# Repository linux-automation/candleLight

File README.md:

# candleLight

A candleLight is a flash drive sized USB CAN dongle.
It works with the
[candle-usb candleLight firmware](https://github.com/candle-usb/candleLight_fw).

This is a fork of [HubertD's candleLight](https://github.com/HubertD/candleLight)
KiCAD project. Thanks for sharing this awesome design as open hardware!

## Releases

### candlelight-S01-R01

This is our first release for production.

* Added Manufacturer and MPN for key components.
* Added our logo.
* Created manufacturing data.

### V1.1

This is HubertD's original release.

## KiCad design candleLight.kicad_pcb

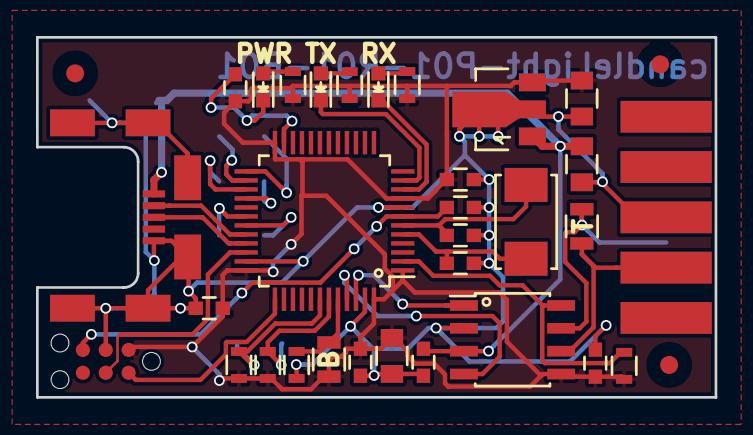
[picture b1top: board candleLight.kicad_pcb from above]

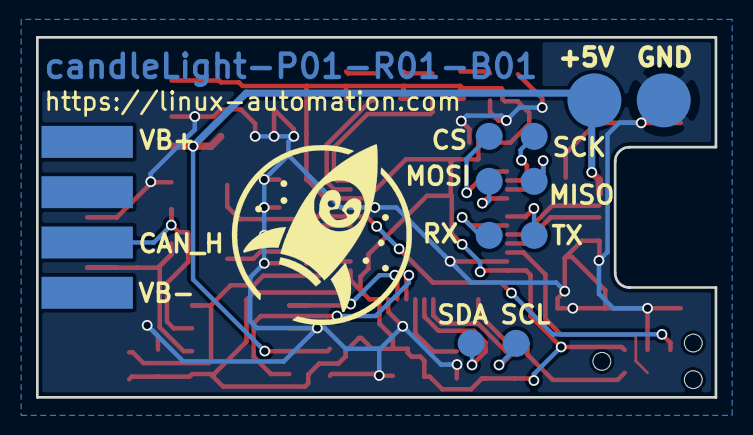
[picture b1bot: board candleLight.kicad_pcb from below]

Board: 2 copper layers, 37.7 x 20.0 mm, 45 parts (11 on the bottom side), 29 nets.

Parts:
C201, C202: 20pF; C_0603
C203, C204, C205, C206, C208, C402, C403: 100nF; C_0603
C207, C301, C303: 10uF; C_0805
D601, D602, D603: LED; LED_0603
FID101, FID102, FID103: Dummy_FIDUCIAL_Passermarke_Type1_RevE_Date16Nov20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; Fiducial_1mm_Dia_2.54mm_Outer_CopperTop
NB101: LAG_logo; lag_rocket_10mmx10.4mm
P501: USB_OTG; Molex-Micro-USB-B-Middle-Mount
R201, R202: 4K7; R_0603
R203: R; R_0805
R204, R601, R602, R603: 1K; R_0603
R401: 10K; R_0603
R402: dnp; R_0805
U201: STM32F072C8Tx; LQFP-48_7x7mm_Pitch0.5mm
U301: MCP1754ST-3302E/MB; SOT89-3_Housing
U401: TJA1051/3; SOIC-8_3.9x4.9mm_Pitch1.27mm
W201, W202, W203, W204, W205, W206, W207, W208: TEST_1P; Measurement_Point_Round-SMD-Pad_Small
W301, W302: TEST_1P; Measurement_Point_Round-SMD-Pad_Big
X501: CON_SWD; TC2030-NL
X502: SUB-D9; DB9M_CI
Y201: 8MHz; ABM3

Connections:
+3V3: C203.1, C204.1, C205.1, C206.1, C207.1, C303.1, C403.1, R201.1, R202.2, R203.1, R401.1, R601.2, R602.2, R603.2, U201.1, U201.9, U201.24, U201.36, U201.48, U301.3, U401.5, X501.1
+5V: C301.1, C402.1, P501.1, U301.1, U401.3, W301.1
/CAN/CAN_H: R402.1, U401.7, X502.7
/CAN/CAN_L: R402.2, U401.6, X502.2
/CAN/CAN_S: R401.2, U201.2, U401.8
/Connectors/NRST: C208.1, U201.7, X501.5
/Connectors/SWCLK: U201.37, X501.2
/Connectors/SWDIO: U201.34, X501.4
/Connectors/USB_DM: P501.2, U201.32
/Connectors/USB_DP: P501.3, U201.33
/LEDs/LED1: D601.1, U201.10
/LEDs/LED2: D602.1, U201.11
/MCU/BOOT0: R203.2, R204.2, U201.44
/MCU/CAN_RX: U201.45, U401.4
/MCU/CAN_TX: U201.46, U401.1
/MCU/CS: U201.25, W205.1
/MCU/MISO: U201.27, W207.1
/MCU/MOSI: U201.28, W208.1
/MCU/RX: U201.31, W202.1
/MCU/SCK: U201.26, W206.1
/MCU/SCL: R201.2, U201.42, W203.1
/MCU/SDA: R202.1, U201.43, W204.1
/MCU/TX: U201.30, W201.1
GND: C201.1, C202.1, C203.2, C204.2, C205.2, C206.2, C207.2, C208.2, C301.2, C303.2, C402.2, C403.2, D603.1, P501.5, P501.6, R204.1, U201.8, U201.23, U201.35, U201.47, U301.2, U401.2, W302.1, X501.3, X502.3
unnamed: C201.2, U201.5, Y201.1
unnamed: C202.2, U201.6, Y201.2
unnamed: D601.2, R601.1
unnamed: D602.2, R602.1
unnamed: D603.2, R603.1

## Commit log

2021-03-03 Perform automatic KiCAD rescue operations
2021-03-03 Add Linux Automation page layout
2021-03-03 Add Fit, Manufacturer, MPN fields
2021-03-04 Update Silkscreen and add netnames
2021-03-04 Add Cap voltage rating, Put PCB ref on cupper, add note for variants
2021-03-04 Add linux automation logo
2021-03-05 Create release candlelight-S01-R01
2021-03-08 Fix candlelight-S01-R01-V03: mixup USB/D-SUB
2021-03-08 Remove original manufacturing data
    The original manufacturing data does not match our
    versioning scheme and we are not going to support
    hardware manufactured based on it.
    Remove it to prevent confusing people looking for
    the manufacturing data corresponding to the product
    they bought in our shop.
2021-03-08 Add PnP information to SMT variant and check BoM completeness
2021-03-09 pcb: Add Layer Stack to drawing frame and regenerate gerber
2021-03-15 Add README.md
2021-03-22 S01-R01: Add BOM as XLS
2021-03-31 Micro-USB socket was marked as THT not SMD. Fixed PnP
2021-04-07 Fix BOM in release R01
2021-06-09 release: Add GenCad Flying probe data
2023-01-24 Add CAN pinout drawing
2023-02-06 Add 3D-printable case
    This is a FreeCAD model of a 3d-printable case for the candlelight.
    It is intended to be printed with ABS or PETG and to mechanically
    protect the candlelight.
    Boths halfs can be screwed together using 2 or 4 M3x8mm cylinder head
    scrwes.
    LEDs are still somewhat visible through holes in the upper part of the
